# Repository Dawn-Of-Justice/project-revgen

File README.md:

# RevGen

A voice-controlled replacement for two remote controls, in Malayalam.

Built for a grandmother who knows perfectly well what the television and the
set-top box are — she just cannot tell which of the two remotes does what. She
presses one button, says what she wants, and hears a confirmation.

```
"TV ഓണാക്കുവോ? ഉം. and sound-ഉം കൂടെ കൂട്ടണേ കുറച്ച്."
   → tv.power, wait 2.5s, tv.volume_up ×2
   → "ടിവി ഓണാക്കി. ശബ്ദം കൂട്ടി."
```

That is a real transcript, not an illustration. Saaras handled the code-mixing,
the filler and the polite interrogative ending on the first attempt.

## Where it stands

| Phase | | |
|---|---|---|
| **0 — does it understand her?** | ✅ | Saaras + Sarvam-105B resolve her speech to the right two actions |
| **1 — emitter** | firmware written, protocol verified | needs hardware to flash |
| **2 — backend** | ✅ deployed | `project-revgen.fly.dev`, verified end to end in ~3.9s |
| **3 — handheld** | ✅ **working** | press, speak, understood, spoken reply. OTA updatable. |
| **4 — harden** | not started | enclosure, battery, undo, watchdogs |

The handheld works on real hardware: one press, hold to talk, release, and the
backend returns the right IR plan with a spoken Malayalam confirmation. It
updates over WiFi, so it stays fixable once it is sealed in a case.

**PCB A3 corrects the amplifier for component-side-up mounting.** See the
[correction record](pcb/remote/A3_CORRECTIONS.md). Owned-part fit and charging
measurements remain pending. Use A3 files; A2 is superseded and A1 was rejected.

The 120 x 45 mm rounded remote carrier PCB is routed, with Gerber/drill exports
and zero reported DRC/ERC violations. See [assembly and fabrication files](pcb/README.md). Charging components have not been tested on
the breadboard, and charging-related firmware behavior remains pending. First
charging tests are planned on the PCB prototype.

The emitter firmware is validated against `backend/tools/fake_emitter.py`, which
impersonates it over the real broker using the same validation rules. Physical
IR emission still needs hardware testing, as does the handheld charging path.

Two blockers, both waiting on parts:

- `stb.digit_1` is byte-identical to `channel_down`, a copy-paste bug inherited
  from v1. The backend refuses to fire it rather than changing the channel she
  did not ask for, so any channel containing a 1 is unavailable until the codes
  are recaptured with an IR receiver.
- Every channel number in `config/commands.json` is `null`, so `channel_set`
  correctly refuses everything. That one just needs five minutes with her
  set-top box.

## Layout

| Path | What it is | State |
|---|---|---|
| `backend/` | STT → intent → resolver → MQTT → TTS | **deployed**, 66 tests |
| `Dockerfile`, `fly.toml` | Deploy config, at the root because the image needs `config/` | live |
| `config/commands.json` | IR codes, channels, Malayalam phrases — single source of truth | needs her channel numbers |
| `firmware/selftest/` | Flash to any new board first: PSRAM, flash, WiFi survey | verified |
| `firmware/audiotest/` | Speaker bring-up: tones only, no network | verified |
| `firmware/capture/` | Phase 0 rig: recapture IR codes, sweep for discrete ones | written, untested on hardware |
| `firmware/emitter/` | IR blaster by the TV | written, untested on hardware |
| `firmware/remote/` | The handheld | **working on hardware** |
| `archive/v1/` | Superseded v1 code, kept for provenance | — |
| `docs/` | Pinouts, spec sheet, parts list | — |
| [`ARCHITECTURE.md`](ARCHITECTURE.md) | Why it is built this way, and what was rejected | — |
| [`docs/BOM.md`](docs/BOM.md) | Parts, with the specs that actually matter | ₹355 outstanding |
| [`docs/WIRING.md`](docs/WIRING.md) | Pin assignment, breadboard wiring, bring-up order | — |
| [`docs/PCB.md`](docs/PCB.md) | Carrier board: netlist, footprints, layout rules | routed; DRC/ERC pass; prototype files ready |
| [`docs/netlist.json`](docs/netlist.json) | Same netlist, machine-checkable against the schematic | 17 nets, 75 connections |

## Start here

```bash
cd backend
python -m venv .venv && source .venv/bin/activate   # Windows: .\.venv\Scripts\Activate.ps1
pip install -r requirements-dev.txt
pytest                      # 66 tests, no network or hardware needed
```

With a Sarvam key and broker credentials in `backend/.env`:

```bash
python tools/check_sarvam.py recordings/    # does it understand her?
python tools/fake_emitter.py                # stand in for the hardware
python tools/send_wav.py recordings/01_tv_on__power_on.m4a https://project-revgen.fly.dev/command
```

See [`backend/README.md`](backend/README.md) for the detail.

## Design in one paragraph

The language model never emits button presses — it returns *goals*
(`power_on`, `volume_up`) from a fixed vocabulary, and plain Python turns goals
into IR. That split exists because IR is open-loop and most buttons are toggles:
firing `tv.power` at a television that is already on turns it off, and no model
can know which case it is in. The safety rules that prevent that live in
`backend/app/resolver.py`, which has no I/O and is entirely unit tested.

## A note on secrets

This repo is public. A Groq key was committed in `.env` in April 2025 and had to
be revoked. Credentials now live in gitignored files — `backend/.env` and
`firmware/emitter/secrets.h` — with committed `.example` templates alongside.
Assume anything pushed here is scraped within minutes.

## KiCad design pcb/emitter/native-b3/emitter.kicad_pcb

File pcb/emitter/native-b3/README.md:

# Emitter B3 — centered LEDs and side USB

Latest enclosure-oriented layout, 2026-09-09. Supersedes B2's placement while
preserving its electrical circuit. Created and routed through KiCad MCP with
Freerouting and local KiCad geometry/net verification helpers.

- Board remains 80 x 65 mm, 1.6 mm thick, two layers, 1 oz copper.
- Four LED body centers are at x=25,35,45,55 mm from the left edge and y=5 mm
  from the front edge. Their group is exactly centered on the board.
- ESP32 is rotated 90 degrees: USB toward the right side, antenna toward the
  copper-free left area. Its reserved module envelope meets the right edge.
  Header spacing remains 25.40 mm with 2.54 mm pin pitch. Pad 1 is lower left.
- The right-side USB centreline is nominally 40.3 mm from the front edge,
  assuming the connector is centered between header rows. Actual connector
  offset, projection, height, shell size and cable clearance are NOT measured.
  Measure these on the owned board before finalizing the printed case opening.
- Mounting holes: 3.2 mm, at (4,25), (4,60), (76,60) mm from the top-left corner.
- J1 is the learning receiver header: 1=3V3, 2=GND, 3=IR OUT to GPIO15.
  It is not a power input. Wire the receiver according to its actual pinout;
  select a part explicitly supporting 3.3 V operation. Provide an IR-transparent
  window or opening in the case for reception and transmission.
- SW1 remains the GPIO27 learning button. Provide access through the lid.

Final checks after audit fixes (2026-09-09): KiCad PCB DRC with all-track errors,
schematic parity, all severities and zone refill reports zero violations, zero
unconnected pads and zero schematic parity issues (`strict-drc.txt`). Schematic
ERC also reports zero errors and zero warnings. The custom library was upgraded
with KiCad's native symbol upgrader and its schematic cache refreshed; warnings
were fixed rather than excluded. Placement has no courtyard overlaps or boundary
violations. All 45 functional pads match the expected net map.

C2 is now at (110.5,73.3) mm, beside Q1 at (111,70), with a short local ground
connection and rerouted supply. PCB net names now exactly match schematic names,
including the leading slash. Description and Datasheet fields are synchronized.
The Gerber ZIP and preview were regenerated after these fixes.

Open `emitter.kicad_pcb`; `emitter-pcb-top.png` is the preview. `fabrication/`
holds B3 Gerbers and drill files. Use `../emitter-B3-prototype-gerbers.zip`
for this placement.

Component values, footprint dimensions and electrical precautions are unchanged;
see `ASSEMBLY.md`, with the orientations and mounting coordinates
above taking precedence. LED 3D models are generic upright placeholders. Form
outer LED leads outward and inner LEDs forward as the case requires; centered
placement alone does not establish IR coverage. USB power capacity, receiver
capture and physical replay remain untested on this revision. These physical
checks cannot be cleared through CAD: actual USB dimensions, VIN voltage under
USB power and receiver model/pinout are still needed from the owned hardware.

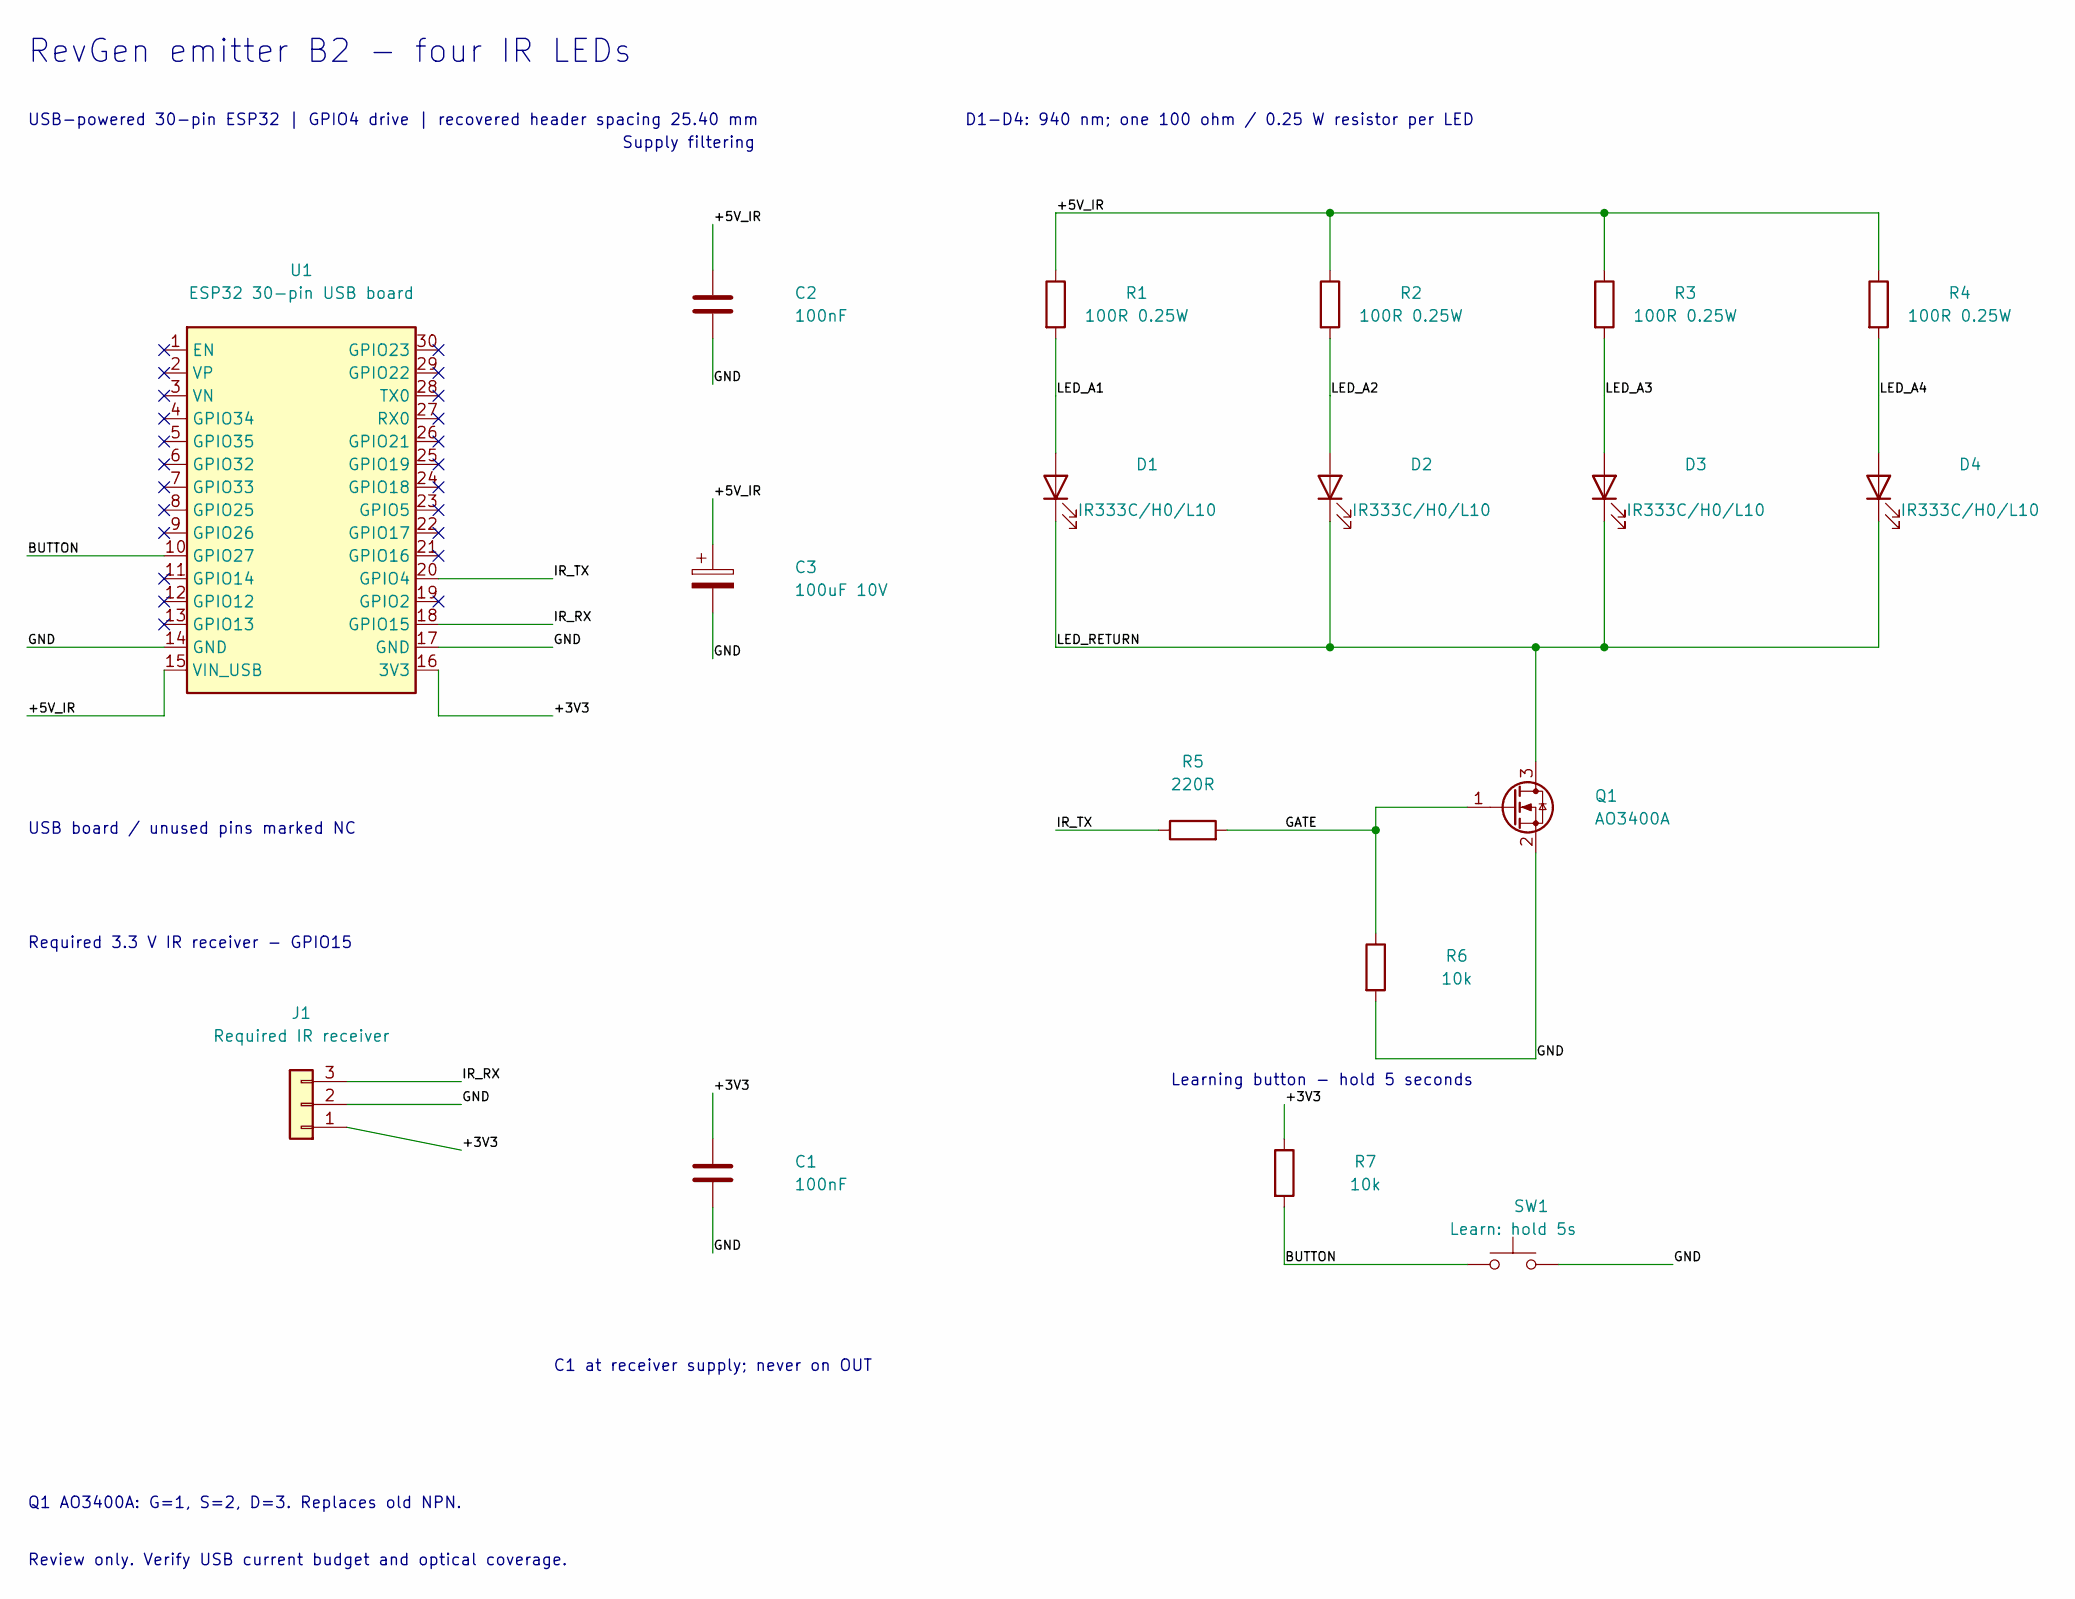
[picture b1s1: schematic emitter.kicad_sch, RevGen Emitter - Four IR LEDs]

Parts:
C1, C2: 100nF; C_Disc_D5.0mm_W2.5mm_P2.50mm
C3: 100uF 10V; CP_Radial_D6.3mm_P2.50mm
D1, D2, D3, D4: IR333C/H0/L10; LED_D5.0mm
J1: Required IR receiver; PinHeader_1x03_P2.54mm_Vertical
Q1: AO3400A; SOT-23
R1, R2, R3, R4: 100R 0.25W; R_Axial_DIN0207_L6.3mm_D2.5mm_P7.62mm_Horizontal
R5: 220R; R_Axial_DIN0207_L6.3mm_D2.5mm_P7.62mm_Horizontal
R6, R7: 10k; R_Axial_DIN0207_L6.3mm_D2.5mm_P7.62mm_Horizontal
SW1: Learn: hold 5s; SW_PUSH_6mm
U1: ESP32 30-pin USB board; ESP32_30pin_recovered

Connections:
/+3V3: C1.1, J1.1, R7.1, U1.16 (3V3)
/+5V_IR: C2.1, C3.1, R1.1, R2.1, R3.1, R4.1, U1.15 (VIN_USB)
/BUTTON: R7.2, SW1.1, U1.10 (GPIO27)
/GATE: Q1.1 (G), R5.2, R6.1
/GND: C1.2, C2.2, C3.2, J1.2, Q1.2 (S), R6.2, SW1.2, U1.14 (GND), U1.17 (GND)
/IR_RX: J1.3, U1.18 (GPIO15)
/IR_TX: R5.1, U1.20 (GPIO4)
/LED_A1: D1.2 (A), R1.2
/LED_A2: D2.2 (A), R2.2
/LED_A3: D3.2 (A), R3.2
/LED_A4: D4.2 (A), R4.2
/LED_RETURN: D1.1 (K), D2.1 (K), D3.1 (K), D4.1 (K), Q1.3 (D)

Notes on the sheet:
RevGen emitter B2 - four IR LEDs
USB-powered 30-pin ESP32 | GPIO4 drive | recovered header spacing 25.40 mm
USB board / unused pins marked NC
Supply filtering
D1-D4: 940 nm; one 100 ohm / 0.25 W resistor per LED
Required 3.3 V IR receiver - GPIO15
C1 at receiver supply; never on OUT
Learning button - hold 5 seconds
Q1 AO3400A: G=1, S=2, D=3. Replaces old NPN.
Review only. Verify USB current budget and optical coverage.

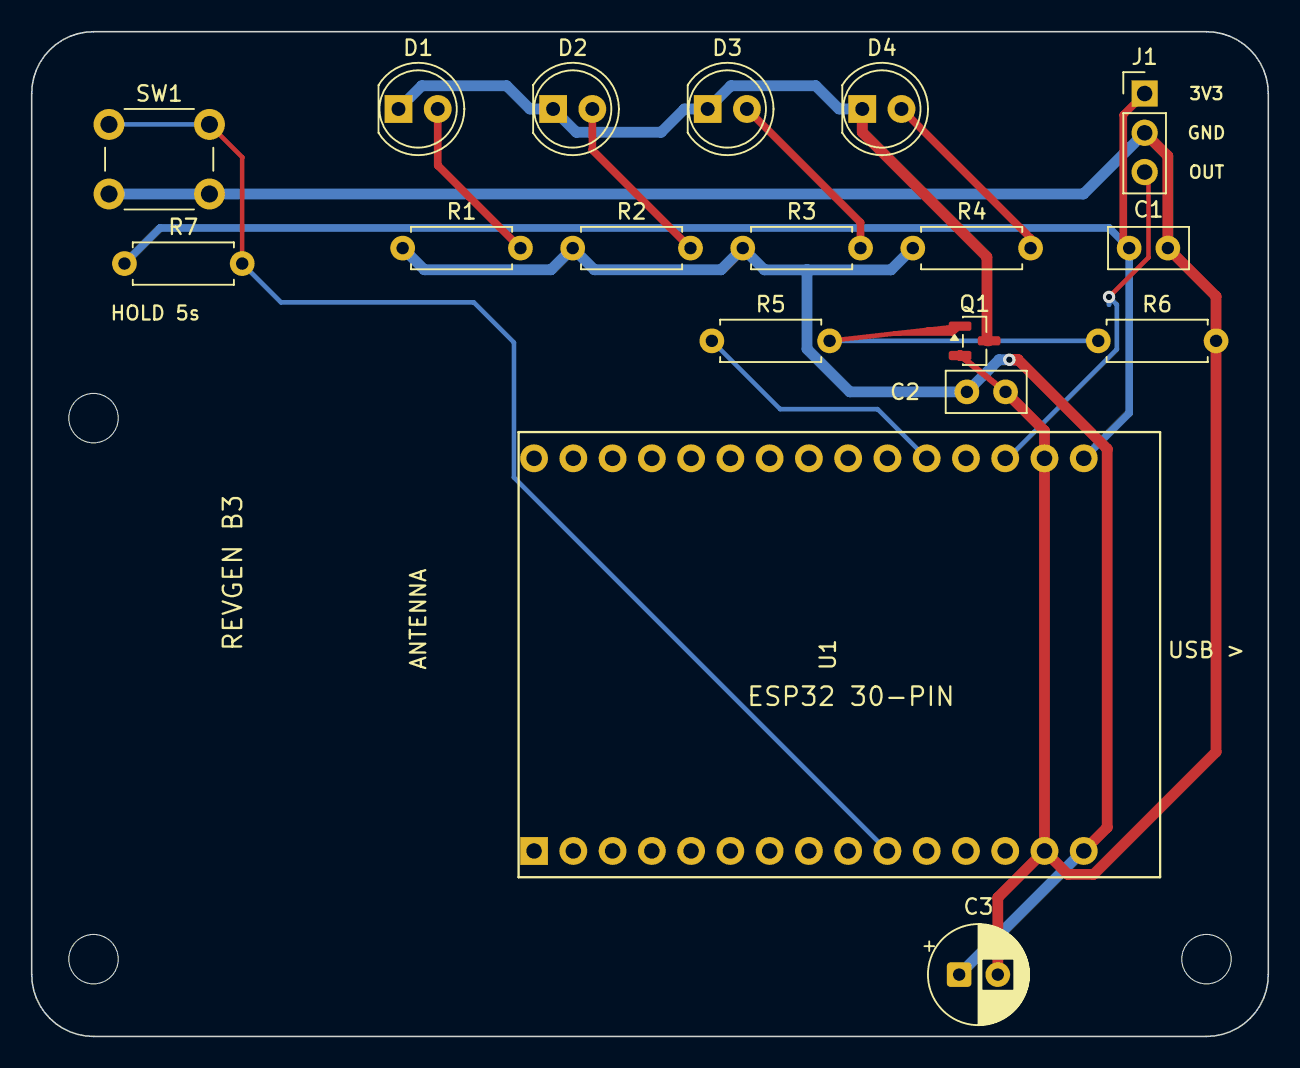
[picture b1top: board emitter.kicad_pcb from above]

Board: 2 copper layers, 80.0 x 65.0 mm, 21 parts (0 on the bottom side), 12 nets.

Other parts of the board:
MH1, MH2, MH3: MountingHole_3.2mm_M3

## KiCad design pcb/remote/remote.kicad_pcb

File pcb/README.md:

# Remote carrier PCB — A3 prototype

> **A3 replaces A2 and rejected A1 files, correcting amplifier component-up mounting.** Mask openings, switch rating, amplifier protection and native schematic parity are corrected. Check owned-part fit before ordering; charging remains untested.

Completed **120 × 45 mm**, rounded R8, two-layer carrier for existing modules.
Fully routed: **0 DRC violations, 0 unconnected items, 0 ERC messages** under
project rules. All 79 logical pad assignments match the schematic.

- [Manufacturing ZIP](remote/RevGen-Remote-A3-Gerbers.zip)
- [KiCad project](remote/remote.kicad_pro), [PCB](remote/remote.kicad_pcb), [schematic](remote/remote.kicad_sch)
- [Assembly instructions](remote/ASSEMBLY.md)
- [A3 amplifier correction](remote/A3_CORRECTIONS.md)
- [Board preview](remote/artifacts/remote-top.png), [1:1 footprint drawing](remote/artifacts/assembly-1to1.svg), [schematic drawing](remote/artifacts/remote.svg)

Core remote operation was verified on breadboard. Charging hardware and charging
firmware remain untested. Compare the owned mic and button with the 1:1 drawing
before ordering; CAD checks do not establish their physical fit.
The separate 24 kHz playback compatibility finding remains open; see
[fresh review](remote/A2_FRESH_REVIEW.md).

The native schematic is authoritative. A2 adds R6 (2.2 kΩ), R7 (10 kΩ), and
a C&K 1101M2S3CQE2 switch. [Correction record](remote/A2_CORRECTIONS.md). Keep `revgen.pretty` and `fp-lib-table`
alongside the project. Superseded manufacturing archives, Trace drafts, routing
intermediates and one-off layout scripts have been removed. The correction and
review records remain as supporting documentation for A3. Final reports are
`artifacts/final-drc.json` and `artifacts/erc.txt`.

Validate from the repository root with KiCad 10 on PATH:

```powershell
kicad-cli sch export netlist --format kicadxml --output pcb/remote/artifacts/netlist.xml pcb/remote/remote.kicad_sch
python pcb/check_netlist.py pcb/remote/artifacts/netlist.xml
kicad-cli sch erc --output pcb/remote/artifacts/erc.txt pcb/remote/remote.kicad_sch
kicad-cli pcb drc --schematic-parity --format json --output pcb/remote/artifacts/final-drc.json pcb/remote/remote.kicad_pcb
& 'C:/Program Files/KiCad/10.0/bin/python.exe' pcb/check_board.py
```

Run `pcb/audit_preorder.py` with KiCad Python to check masks, full parity and
the A3 ZIP against current exports. `pcb/check_amplifier_orientation.py` checks
the module orientation against the retained manufacturer reference.
`pcb/package_a3.py` packages the checked native project and manufacturing exports;
it does not regenerate the layout.

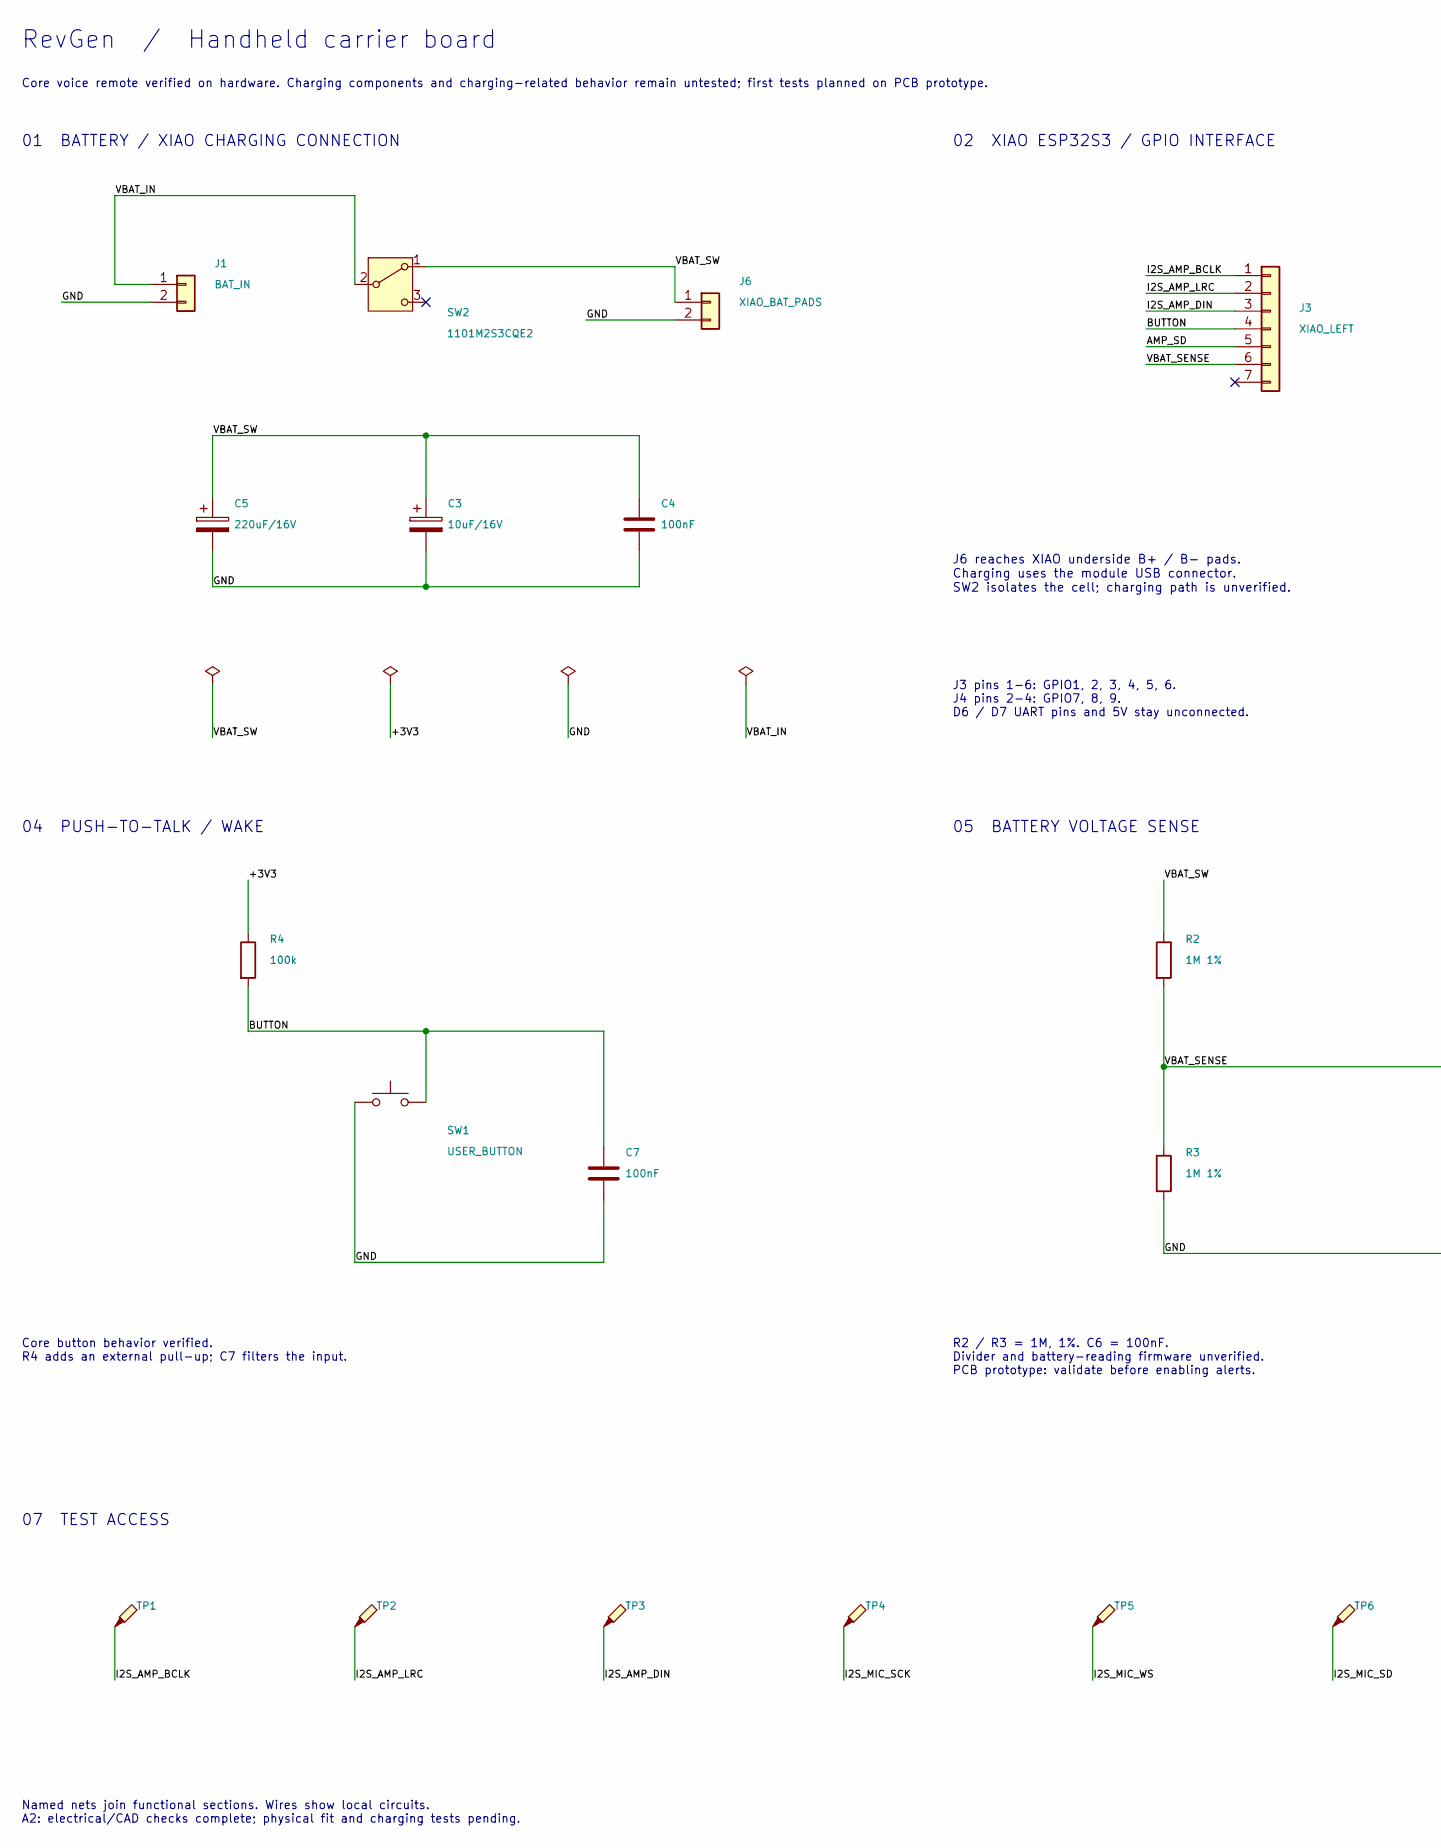
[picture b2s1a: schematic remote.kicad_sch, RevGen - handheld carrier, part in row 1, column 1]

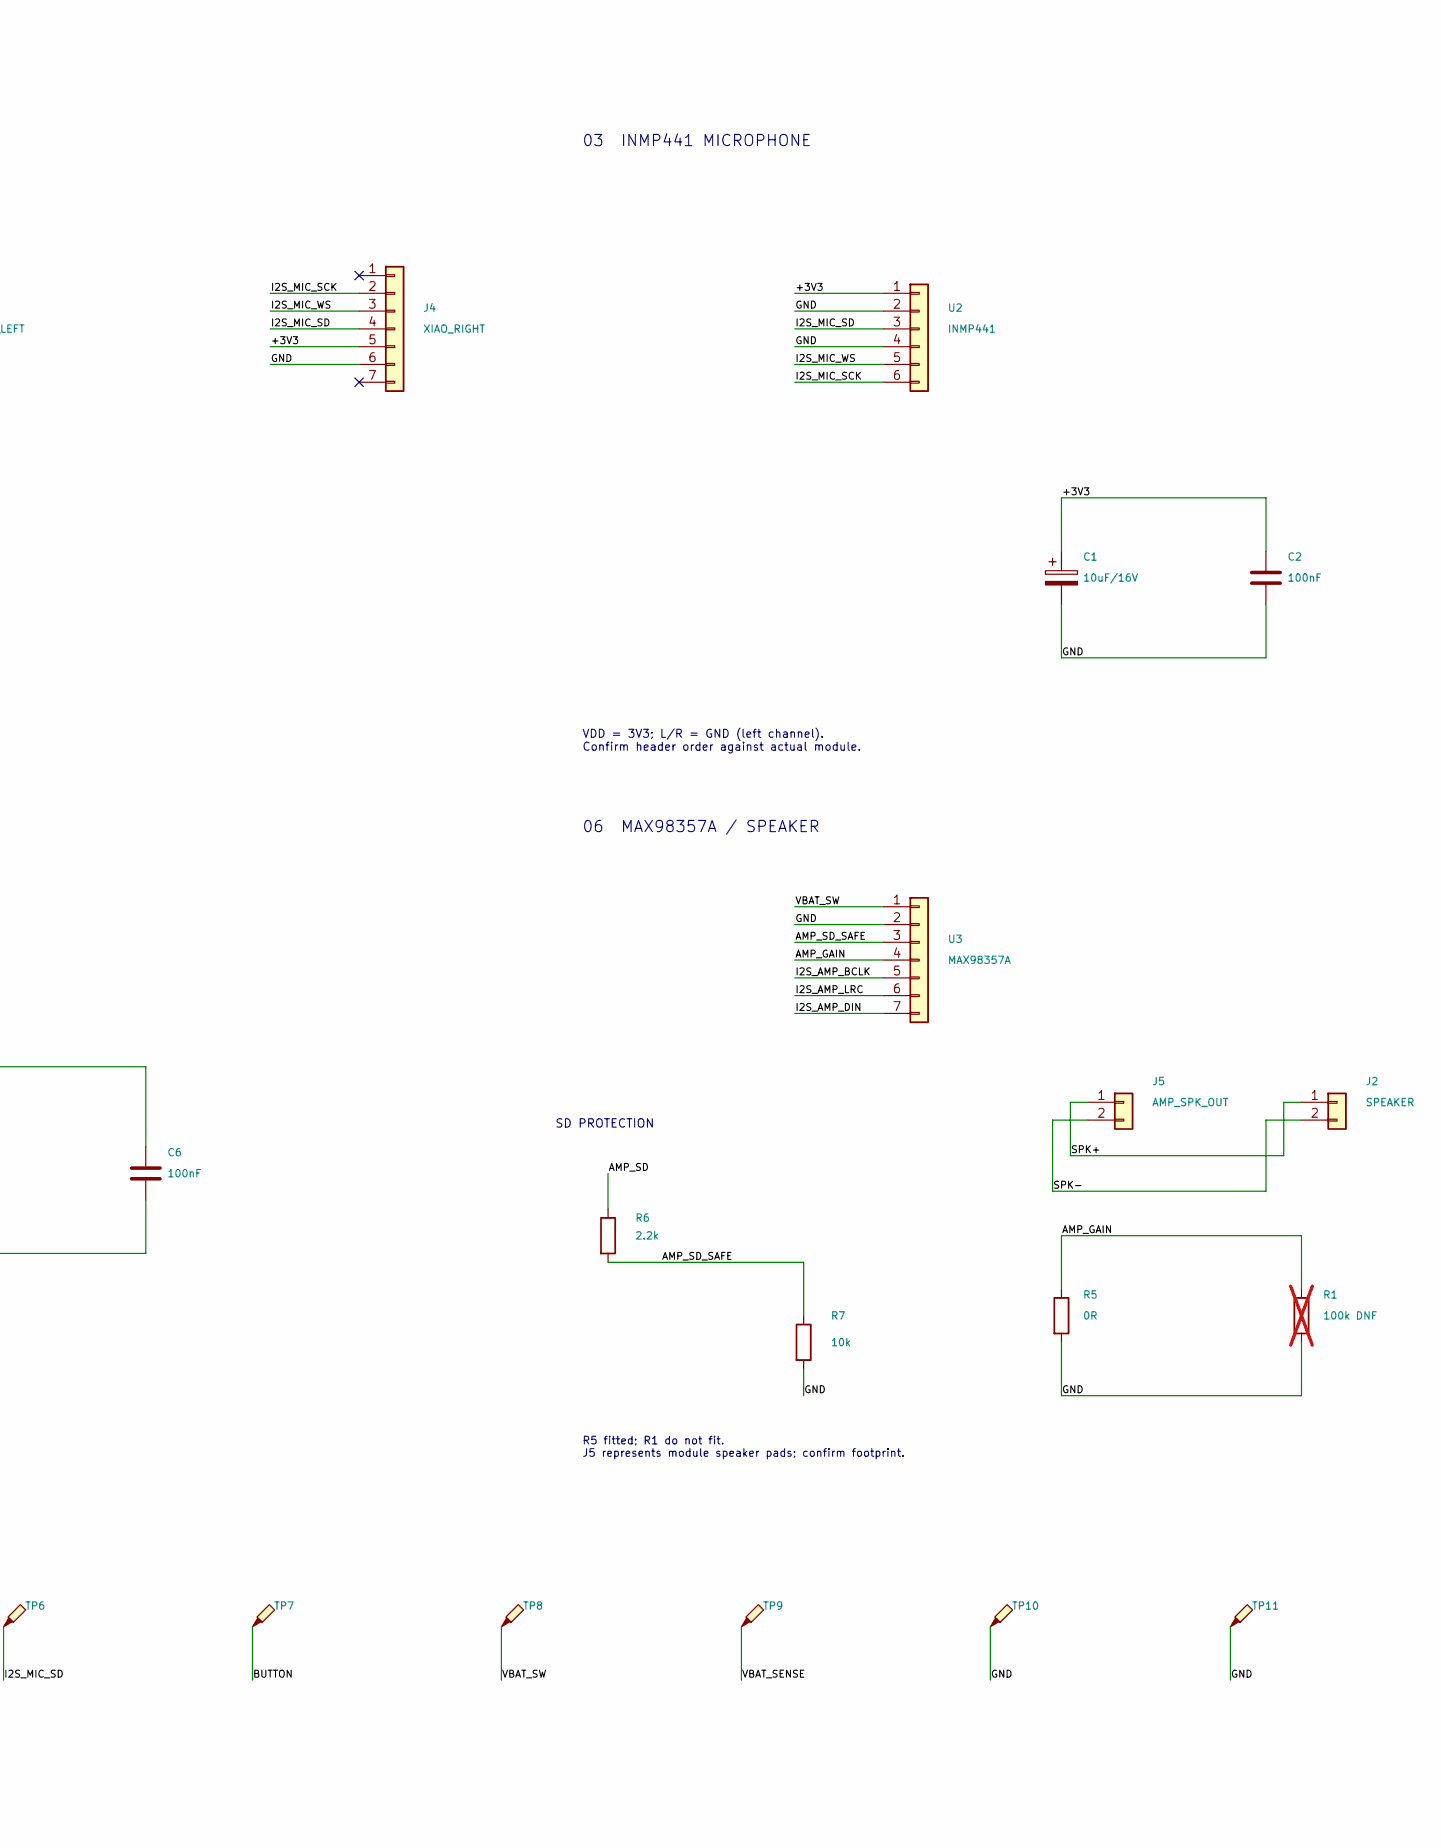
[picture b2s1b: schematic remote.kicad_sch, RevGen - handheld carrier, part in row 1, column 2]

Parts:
C1, C3: 10uF/16V; CP_Radial_D6.3mm_P2.50mm
C2, C4, C6, C7: 100nF; C_Disc_D5.0mm_W2.5mm_P5.00mm
C5: 220uF/16V; CP_Radial_D6.3mm_P2.50mm
J1: BAT_IN; JST_PH_S2B-PH-K_1x02_P2.00mm_Horizontal
J2: SPEAKER; JST_PH_B2B-PH-K_1x02_P2.00mm_Vertical
J3: XIAO_LEFT; XIAO_Left
J4: XIAO_RIGHT; XIAO_Right
J5: AMP_SPK_OUT; MAX98357A_Adafruit_Speaker
J6: XIAO_BAT_PADS; XIAO_Battery_SolderAccess
R1: 100k DNF; R_Axial_DIN0207_L6.3mm_D2.5mm_P10.16mm_Horizontal; not fitted
R2, R3: 1M 1%; R_Axial_DIN0207_L6.3mm_D2.5mm_P10.16mm_Horizontal
R4: 100k; R_Axial_DIN0207_L6.3mm_D2.5mm_P10.16mm_Horizontal
R5: 0R; R_Axial_DIN0207_L6.3mm_D2.5mm_P10.16mm_Horizontal
R6: 2.2k; R_Axial_DIN0207_L6.3mm_D2.5mm_P10.16mm_Horizontal
R7: 10k; R_Axial_DIN0207_L6.3mm_D2.5mm_P10.16mm_Horizontal
SW1: USER_BUTTON; SW_SPST_Omron_B3F-40xx
SW2: 1101M2S3CQE2; SW_CK_1101M2S3CQE2
TP1: TP_I2S_AMP_BCLK; TestPoint_THTPad_D1.5mm_Drill0.7mm
TP2: TP_I2S_AMP_LRC; TestPoint_THTPad_D1.5mm_Drill0.7mm
TP3: TP_I2S_AMP_DIN; TestPoint_THTPad_D1.5mm_Drill0.7mm
TP4: TP_I2S_MIC_SCK; TestPoint_THTPad_D1.5mm_Drill0.7mm
TP5: TP_I2S_MIC_WS; TestPoint_THTPad_D1.5mm_Drill0.7mm
TP6: TP_I2S_MIC_SD; TestPoint_THTPad_D1.5mm_Drill0.7mm
TP7: TP_BUTTON; TestPoint_THTPad_D1.5mm_Drill0.7mm
TP8: TP_VBAT_SW; TestPoint_THTPad_D1.5mm_Drill0.7mm
TP9: TP_VBAT_SENSE; TestPoint_THTPad_D1.5mm_Drill0.7mm
TP10: TP_GND_A; TestPoint_THTPad_D1.5mm_Drill0.7mm
TP11: TP_GND_B; TestPoint_THTPad_D1.5mm_Drill0.7mm
U2: INMP441; INMP441_Round_ChipUp
U3: MAX98357A; MAX98357A_Adafruit_Input

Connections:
/+3V3: C1.1, C2.1, J4.5, R4.1, U2.1
/AMP_GAIN: R1.1, R5.1, U3.4
/AMP_SD: J3.5, R6.1
/AMP_SD_SAFE: R6.2, R7.1, U3.3
/BUTTON: C7.1, J3.4, R4.2, SW1.2, TP7.1
/GND: C1.2, C2.2, C3.2, C4.2, C5.2, C6.2, C7.2, J1.2, J4.6, J6.2, R1.2, R3.2, R5.2, R7.2, SW1.1, TP10.1, TP11.1, U2.2, U2.4, U3.2
/I2S_AMP_BCLK: J3.1, TP1.1, U3.5
/I2S_AMP_DIN: J3.3, TP3.1, U3.7
/I2S_AMP_LRC: J3.2, TP2.1, U3.6
/I2S_MIC_SCK: J4.2, TP4.1, U2.6
/I2S_MIC_SD: J4.4, TP6.1, U2.3
/I2S_MIC_WS: J4.3, TP5.1, U2.5
/SPK+: J2.1, J5.1
/SPK-: J2.2, J5.2
/VBAT_IN: J1.1, SW2.2 (B)
/VBAT_SENSE: C6.1, J3.6, R2.2, R3.1, TP9.1
/VBAT_SW: C3.1, C4.1, C5.1, J6.1, R2.1, SW2.1 (A), TP8.1, U3.1

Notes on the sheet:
RevGen / Handheld carrier board
Core voice remote verified on hardware. Charging components and charging-related behavior remain untested; first tests planned on PCB prototype.
01 BATTERY / XIAO CHARGING CONNECTION
02 XIAO ESP32S3 / GPIO INTERFACE
03 INMP441 MICROPHONE
04 PUSH-TO-TALK / WAKE
05 BATTERY VOLTAGE SENSE
06 MAX98357A / SPEAKER
07 TEST ACCESS
J6 reaches XIAO underside B+ / B- pads. Charging uses the module USB connector. SW2 isolates the cell; charging path is unverified.
J3 pins 1-6: GPIO1, 2, 3, 4, 5, 6. J4 pins 2-4: GPIO7, 8, 9. D6 / D7 UART pins and 5V stay unconnected.
VDD = 3V3; L/R = GND (left channel). Confirm header order against actual module.
Core button behavior verified. R4 adds an external pull-up; C7 filters the input.
R2 / R3 = 1M, 1%. C6 = 100nF. Divider and battery-reading firmware unverified. PCB prototype: validate before enabling alerts.
R5 fitted; R1 do not fit. J5 represents module speaker pads; confirm footprint.
Named nets join functional sections. Wires show local circuits. A2: electrical/CAD checks complete; physical fit and charging tests pending.
SD PROTECTION

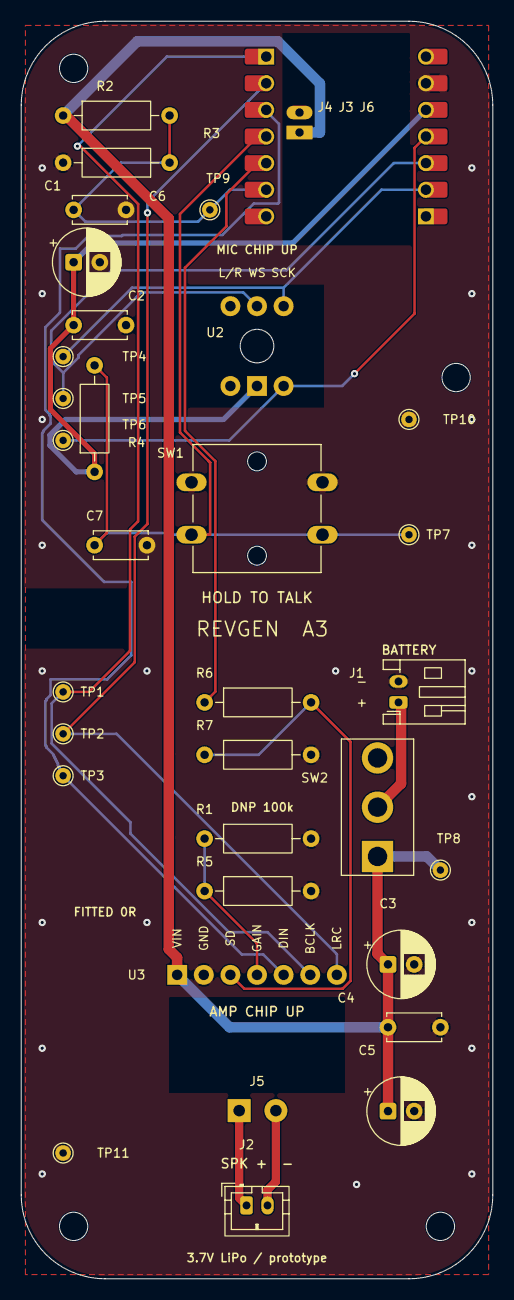
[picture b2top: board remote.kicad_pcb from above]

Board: 2 copper layers, 45.0 x 120.0 mm, 39 parts (0 on the bottom side), 17 nets.

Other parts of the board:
H1, H2, H3, H4: MountingHole_2.7mm_M2.5

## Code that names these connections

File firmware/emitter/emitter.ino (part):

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 * BOARD: ESP32C3 Dev Module, USB CDC On Boot enabled
 *
 * WIRING
 *   B2 carrier: GPIO4 -> 220R -> AO3400A gate; 10k gate-to-source pull-down.
 *   4x IR LED (940nm) in parallel, EACH with its own 100R resistor, from 5V
 *   to the drain. MOSFET source to GND. Button GPIO27, receiver OUT GPIO15.
 *   Do not share one resistor across the LEDs -- they do not current-share and
 *   one ends up doing all the work.
 *   Fan them across roughly 90 degrees so aiming is designed out of the system.
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
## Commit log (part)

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2025-02-03 Add initial implementation of audio processing service with recording and translation features
2025-02-18 Refactor audio processing service to remove hardcoded port and improve environment variable handling
2025-02-18 Remove sample_call.py as part of code cleanup
2025-02-18 Add Flask to requirements for web framework support
2025-02-18 Update audio processing service and requirements
    - Added Google Cloud Translate to requirements
    - Set environment variable for Google credentials in app.py
    - Improved translated text handling in process_audio function
    - Updated sample_call notebook to reflect correct URL
2025-02-18 Add google-cloud-speech to requirements for speech recognition support
2025-02-18 Add Gunicorn for production server and update requirements
2025-02-18 Setup Google Cloud credentials from environment variable and update API endpoint in sample notebook
2025-02-18 Refactor audio processing logic for improved readability and error handling
2025-02-18 Add HTTPS redirection and ProxyFix middleware to enhance security
2025-02-18 Add WebSocket support for audio processing and translation
2025-02-18 Add gevent and monkey patching for improved concurrency support
2025-02-18 Refactor audio processing to improve structure and add WebSocket support for real-time audio handling
2025-04-10 Implement WebSocket audio streaming with reconnection logic and light sleep management
2025-04-12 Implement code changes to enhance functionality and improve performance
2025-05-07 Implement IR Remote Mapping Application with WebSocket and ESP32 Integration
    - Added frontend HTML and JavaScript for managing IR remotes, capturing IR signals, and deploying to ESP32.
    - Created backend server using Express to handle API requests for remotes and buttons, and to manage WebSocket connections for real-time communication.
    - Integrated Serial communication with ESP32 for capturing and sending IR codes.
    - Implemented functionality to save and load IR codes from a JSON file.
    - Established a structure for capturing IR signals and deploying remotes to the ESP32.
2025-06-01 Add IR receiver functionality and basic IR sender example
2025-07-19 Remove obsolete files and configurations related to the IR remote project
    - Deleted gunicorn_config.py, llm.py, record.py, recording.mp3, requirements.txt, sample_call.ipynb, speech.py, and mapping-server files (app.js, index.html, server.js).
    - Removed transmitter-related files including basic_receive.ino and transmitter.ino.
    - Cleared out the requirements.txt to remove unused dependencies.
    - Deleted the recording.mp3 file and the sample Jupyter notebook.
    - Removed the old transmitter.ino file and replaced it with a new structure for better organization.
    - Added a new signal.json file to store remote configurations.
2025-08-24 Implement ESP32 OpenAI Realtime API Client with I2S audio capture and WebSocket communication
